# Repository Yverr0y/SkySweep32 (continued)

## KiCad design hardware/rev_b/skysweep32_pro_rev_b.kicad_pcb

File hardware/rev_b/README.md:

# SkySweep32 Pro Rev B Hardware Architecture

> **EXPERIMENTAL / UNVERIFIED / DO NOT ORDER**
>
> This directory contains a failed Rev B design baseline under engineering
> audit. The checked-in ERC report has 8 warnings and the checked-in DRC report
> has 375 violations, including mounting-hole/component conflicts. Generated
> STEP/STL files and previews do not prove mechanical fit. Do not manufacture
> this revision. See [`HARDWARE_VALIDATION_REPORT.md`](HARDWARE_VALIDATION_REPORT.md).

---

## Key Hardware Improvements (Rev A → Rev B)

1. **Integrated ESP32-S3 MCU**: Replaced generic DevKit module with an integrated **ESP32-S3-WROOM-1-N8** (8 MB flash, no PSRAM) to prevent strap-pin conflicts on GPIO35–37.
2. **Sub-GHz Transceiver Upgrade**: Replaced obsolete 433 MHz CC1101 module with Ebyte **E07-900M10S** (855–925 MHz SMD castellated module) with IPEX pigtail to panel SMA.
3. **Four-Layer PCB Architecture**: Stackup:
   - `L1 (F.Cu)`: High-speed signal routing and local power traces
   - `L2 (In1.Cu)`: Uninterrupted solid Ground plane (`GND`)
   - `L3 (In2.Cu)`: Split Power plane (`3V3_MAIN` / `VBUS_PROTECTED`)
   - `B.Cu`: Secondary signal routing
4. **Enhanced Power Management**:
   - TI **LM73100** eFuse protection (5.5 A, OVLO, UVLO, IMON)
   - Diodes Inc **AP63203WU-7** 2.0 A synchronous buck converter (3.3 V output, 44% headroom)
   - Dedicated low-pass RC filters on all RF power branches
5. **No Decorative SMA Connectors**: Every SMA bulkhead maps 1:1 to an active radio module.
6. **Sentinel Enclosure Rev B**: Generated enclosure concept; assembly fit and interference are unverified.

---

## File Inventory

| File / Path | Description |
|---|---|
| [`skysweep32_pro_rev_b.kicad_sch`](skysweep32_pro_rev_b.kicad_sch) | Native KiCad 10 schematic |
| [`skysweep32_pro_rev_b.kicad_pcb`](skysweep32_pro_rev_b.kicad_pcb) | Native 4-layer KiCad 10 PCB baseline; checked-in DRC currently fails |
| [`generate_pcb.py`](generate_pcb.py) | Automated PCB generation and net-contract assertion script |
| [`build_case_rev_b.py`](build_case_rev_b.py) | FreeCAD Python 3D enclosure CAD synthesis script |
| [`skysweep32_pro_rev_b.step`](skysweep32_pro_rev_b.step) | 3D PCB Assembly STEP file (5.1 MB) |
| [`enclosures/skysweep32_pro_case_bottom_rev_b.stl`](enclosures/skysweep32_pro_case_bottom_rev_b.stl) | Sentinel Enclosure Bottom Case (3D Printable STL) |
| [`enclosures/skysweep32_pro_case_lid_rev_b.stl`](enclosures/skysweep32_pro_case_lid_rev_b.stl) | Sentinel Enclosure Top Lid Case (3D Printable STL) |
| [`HARDWARE_VALIDATION_REPORT.md`](HARDWARE_VALIDATION_REPORT.md) | Evidence-backed current failure and maturity status |

---

## Previews

### 3D PCB Assembly Preview

### Sentinel Enclosure
- Bottom case volume: **43 866.27 mm³**
- Lid case volume: **34 725.00 mm³**
- Wall thickness: **2.5 mm**
- Outer dimensions: **128 × 88 × 28.5 mm**

---

## Build & Synthesis Commands

Generate PCB baseline:
```bash
python hardware/rev_b/generate_pcb.py
```

Run KiCad DRC check:
```bash
kicad-cli pcb drc hardware/rev_b/skysweep32_pro_rev_b.kicad_pcb
```

Generate 3D Enclosure STEP/STL files:
```bash
python hardware/rev_b/build_case_rev_b.py
```

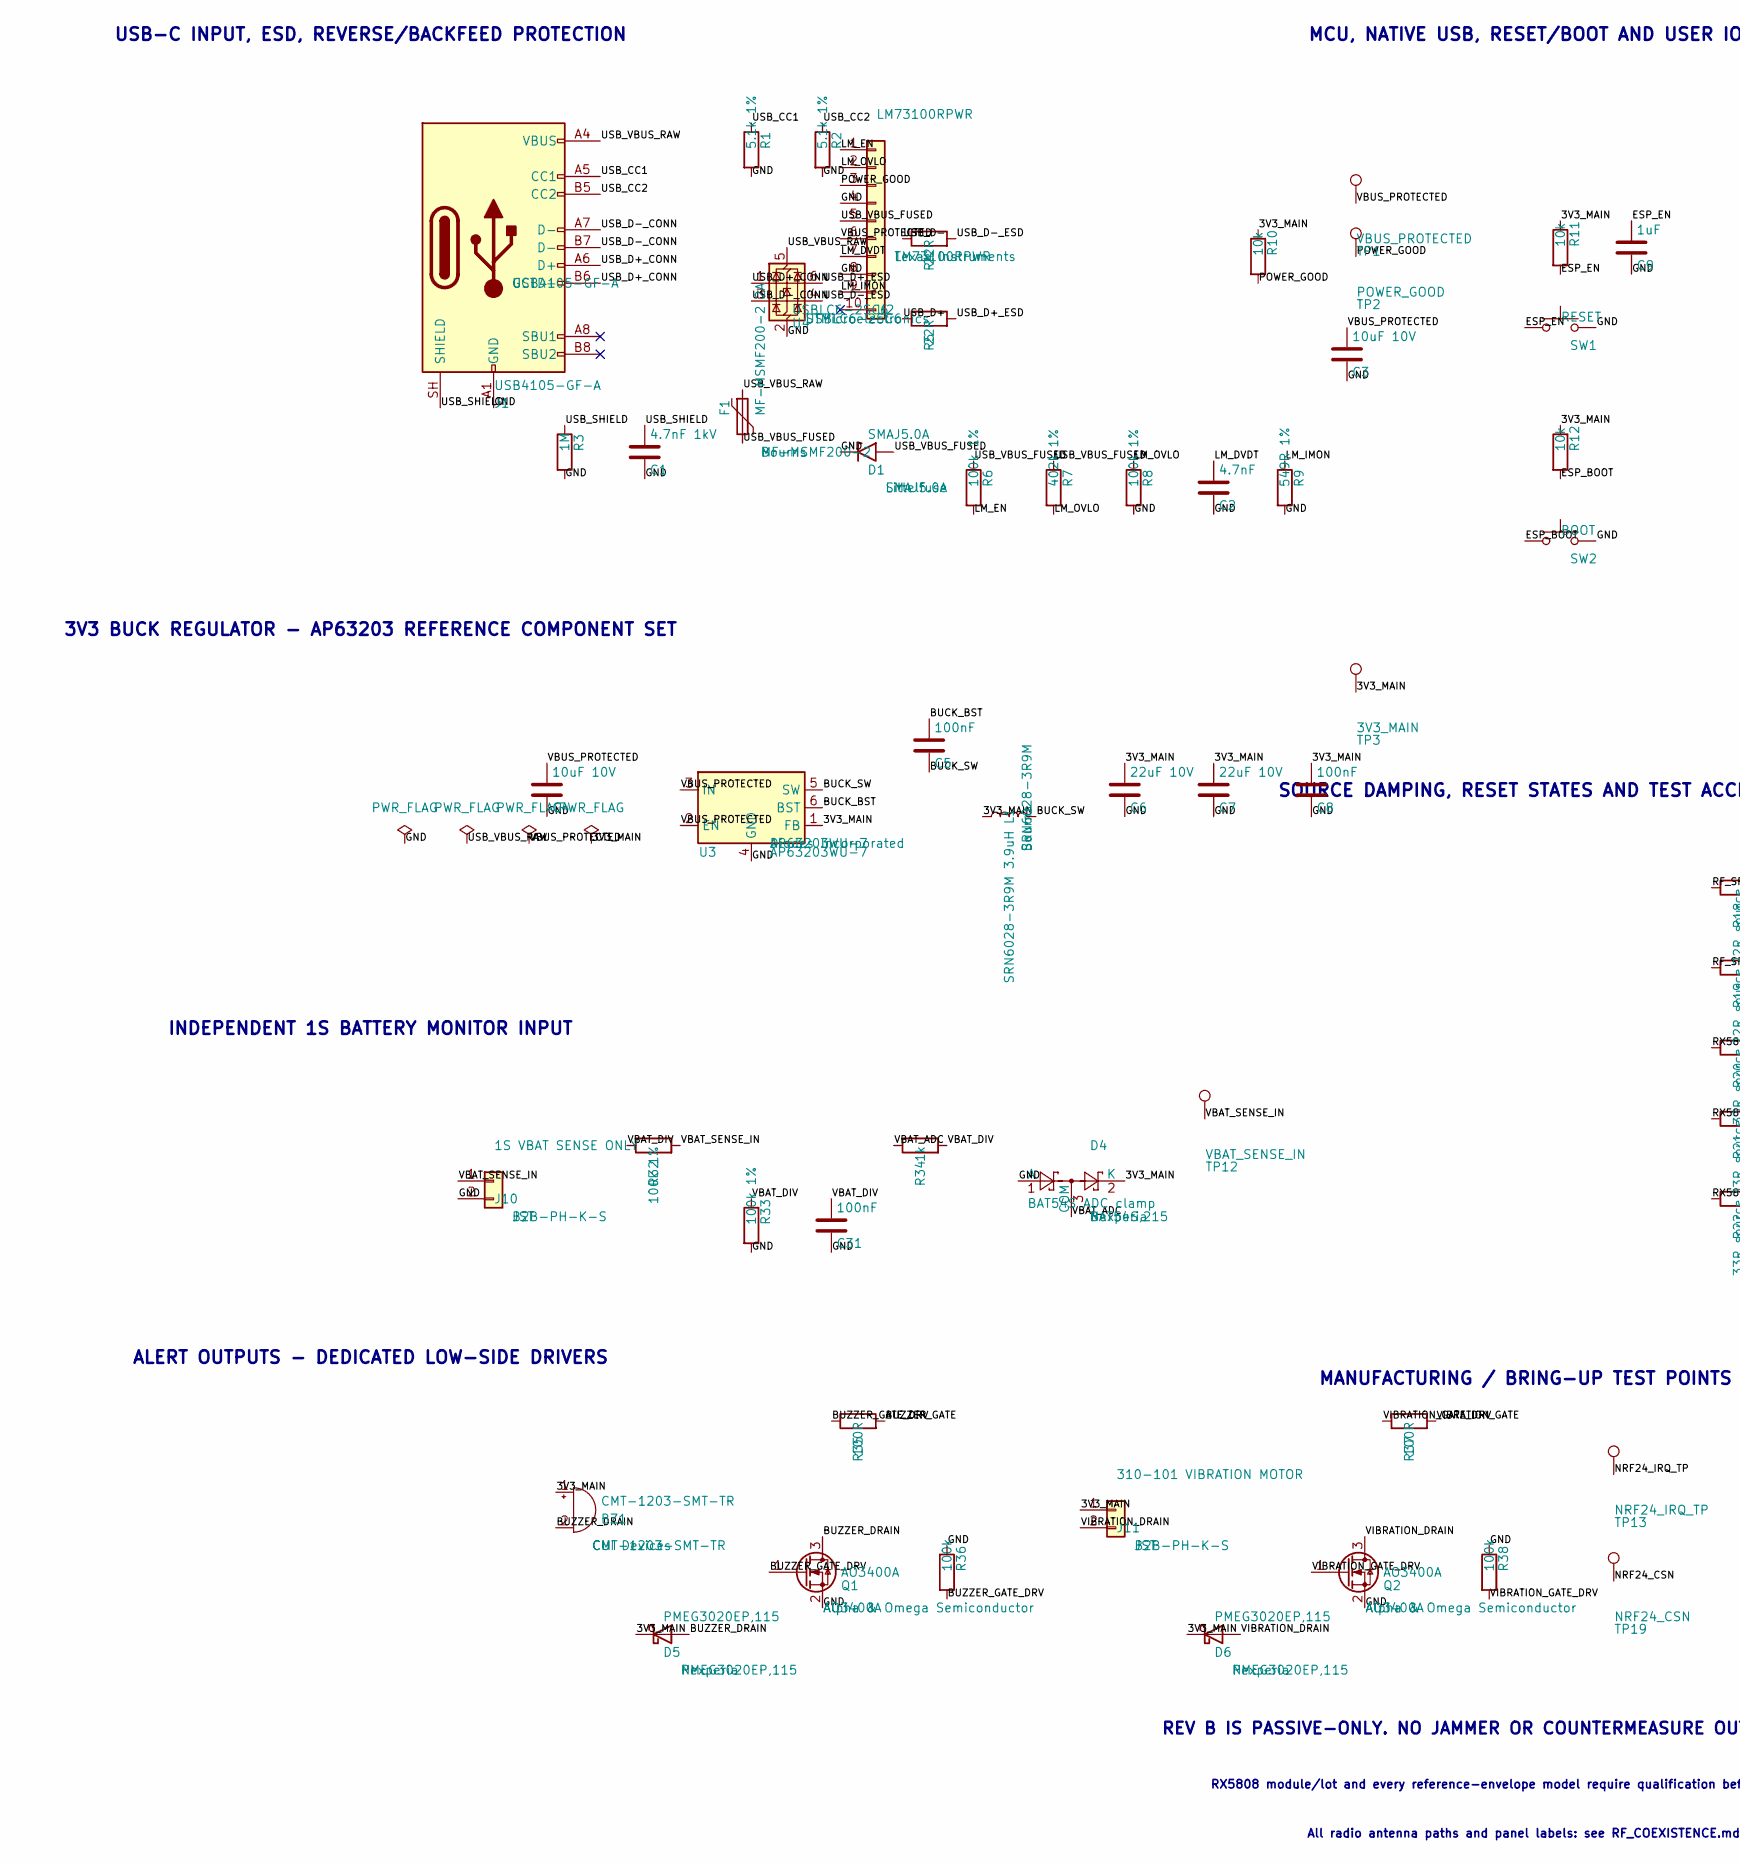
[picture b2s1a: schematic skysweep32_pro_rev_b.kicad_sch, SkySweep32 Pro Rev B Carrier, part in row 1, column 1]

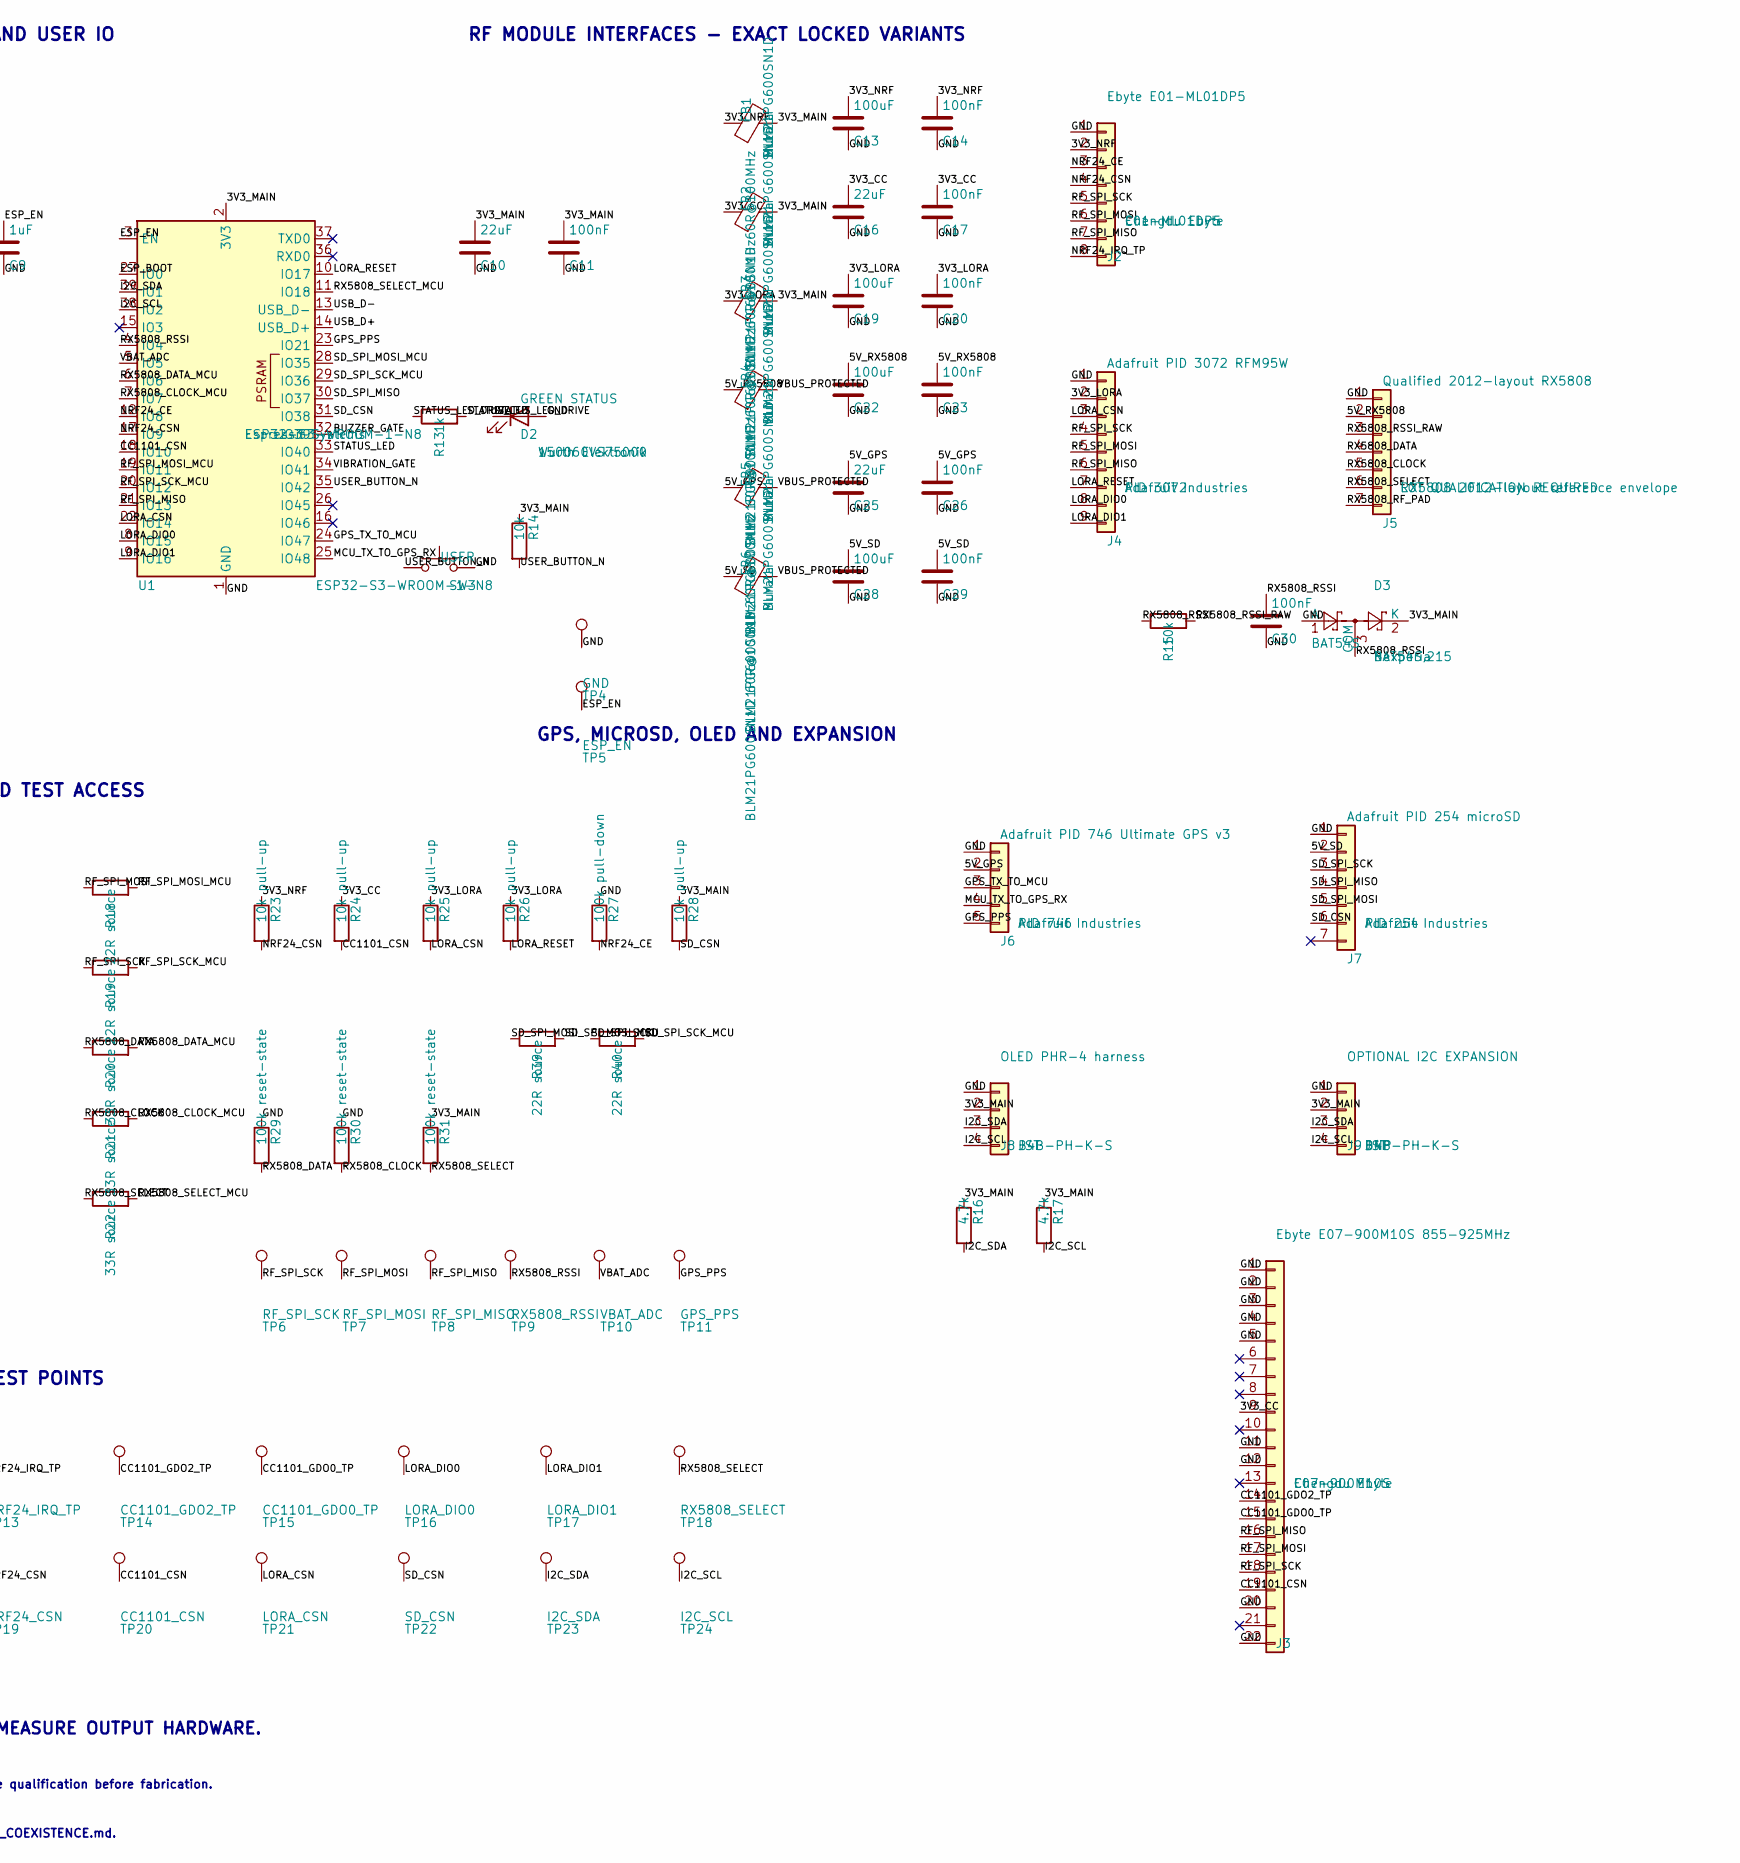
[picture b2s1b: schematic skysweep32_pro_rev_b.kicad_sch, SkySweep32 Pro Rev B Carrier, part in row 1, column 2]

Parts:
BZ1: CMT-1203-SMT-TR; Buzzer_CUI_CMT-1203-SMT-TR; MPN CMT-1203-SMT-TR
C1: 4.7nF 1kV; C_0603_1608Metric
C2: 4.7nF; C_0603_1608Metric
C3, C4: 10uF 10V; C_0805_2012Metric
C5, C8, C11, C14, C17, C20, C23, C26, C29, C30, C31: 100nF; C_0603_1608Metric
C6, C7: 22uF 10V; C_1210_3225Metric
C9: 1uF; C_0603_1608Metric
C10, C16, C25: 22uF; C_1210_3225Metric
C13, C19, C22, C28: 100uF; C_1210_3225Metric
D1: SMAJ5.0A; D_SMA; MPN SMAJ5.0A
D2: GREEN STATUS; LED_0603_1608Metric; MPN 150060VS75000
D3: BAT54S; SOT-23; MPN BAT54S,215
D4: BAT54S ADC clamp; SOT-23; MPN BAT54S,215
D5, D6: PMEG3020EP,115; D_SOD-128; MPN PMEG3020EP,115
F1: MF-MSMF200-2 2A; Fuse_1812_4532Metric; MPN MF-MSMF200-2
FB1, FB2, FB3, FB4, FB5, FB6: BLM21PG600SN1D 60R@100MHz; R_0805_2012Metric; MPN BLM21PG600SN1D
J1: USB4105-GF-A; USB_C_Receptacle_GCT_USB4105-xx-A_16P_TopMnt_Horizontal; MPN USB4105-GF-A
J2: Ebyte E01-ML01DP5; Module_Ebyte_E01_ML01DP5; MPN E01-ML01DP5
J3: Ebyte E07-900M10S 855-925MHz; Module_Ebyte_E07_900M10S; MPN E07-900M10S
J4: Adafruit PID 3072 RFM95W; Module_Adafruit_RFM95W_PID3072; MPN PID 3072
J5: Qualified 2012-layout RX5808; Module_RX5808_2012_QUALIFIED; MPN RX5808 2012-layout reference envelope
J6: Adafruit PID 746 Ultimate GPS v3; Module_Adafruit_GPS_PID746; MPN PID 746
J7: Adafruit PID 254 microSD; Module_Adafruit_MicroSD_PID254; MPN PID 254
J8: OLED PHR-4 harness; JST_PH_B4B-PH-K_1x04_P2.00mm_Vertical; MPN B4B-PH-K-S
J9: OPTIONAL I2C EXPANSION; JST_PH_B4B-PH-K_1x04_P2.00mm_Vertical; MPN B4B-PH-K-S
J10: 1S VBAT SENSE ONLY; JST_PH_B2B-PH-K_1x02_P2.00mm_Vertical; MPN B2B-PH-K-S
J11: 310-101 VIBRATION MOTOR; JST_PH_B2B-PH-K_1x02_P2.00mm_Vertical; MPN B2B-PH-K-S
L1: SRN6028-3R9M 3.9uH; L_Bourns-SRN6028; MPN SRN6028-3R9M
Q1, Q2: AO3400A; SOT-23; MPN AO3400A
R1, R2: 5.1k 1%; R_0603_1608Metric
R3: 1M; R_0603_1608Metric
R4, R5: 22R; R_0603_1608Metric
R6, R8, R32, R33: 100k 1%; R_0603_1608Metric
R7: 402k 1%; R_0603_1608Metric
R9: 549R 1%; R_0603_1608Metric
R10, R11, R12, R14, R15: 10k; R_0603_1608Metric
R13, R34: 1k; R_0603_1608Metric
R16, R17: 4.7k; R_0603_1608Metric
R18, R19, R39, R40: 22R source; R_0603_1608Metric
R20, R21, R22: 33R source; R_0603_1608Metric
R23, R24, R25, R26, R28: 10k pull-up; R_0603_1608Metric
R27: 100k pull-down; R_0603_1608Metric
R29, R30, R31: 100k reset-state; R_0603_1608Metric
R35, R37: 100R; R_0603_1608Metric
R36, R38: 100k; R_0603_1608Metric
SW1: RESET; SW_SPST_PTS810
SW2: BOOT; SW_SPST_PTS810
SW3: USER; SW_SPST_PTS810
TP1: VBUS_PROTECTED; TestPoint_Plated_Hole_D2.0mm
TP2: POWER_GOOD; TestPoint_Plated_Hole_D2.0mm
TP3: 3V3_MAIN; TestPoint_Plated_Hole_D2.0mm
TP4: GND; TestPoint_Plated_Hole_D2.0mm
TP5: ESP_EN; TestPoint_Plated_Hole_D2.0mm
TP6: RF_SPI_SCK; TestPoint_Plated_Hole_D2.0mm
TP7: RF_SPI_MOSI; TestPoint_Plated_Hole_D2.0mm
TP8: RF_SPI_MISO; TestPoint_Plated_Hole_D2.0mm
TP9: RX5808_RSSI; TestPoint_Plated_Hole_D2.0mm
TP10: VBAT_ADC; TestPoint_Plated_Hole_D2.0mm
TP11: GPS_PPS; TestPoint_Plated_Hole_D2.0mm
TP12: VBAT_SENSE_IN; TestPoint_Plated_Hole_D2.0mm
TP13: NRF24_IRQ_TP; TestPoint_Plated_Hole_D2.0mm
TP14: CC1101_GDO2_TP; TestPoint_Plated_Hole_D2.0mm
TP15: CC1101_GDO0_TP; TestPoint_Plated_Hole_D2.0mm
TP16: LORA_DIO0; TestPoint_Plated_Hole_D2.0mm
TP17: LORA_DIO1; TestPoint_Plated_Hole_D2.0mm
TP18: RX5808_SELECT; TestPoint_Plated_Hole_D2.0mm
TP19: NRF24_CSN; TestPoint_Plated_Hole_D2.0mm
TP20: CC1101_CSN; TestPoint_Plated_Hole_D2.0mm
TP21: LORA_CSN; TestPoint_Plated_Hole_D2.0mm
TP22: SD_CSN; TestPoint_Plated_Hole_D2.0mm
TP23: I2C_SDA; TestPoint_Plated_Hole_D2.0mm
TP24: I2C_SCL; TestPoint_Plated_Hole_D2.0mm
U1: ESP32-S3-WROOM-1-N8; ESP32-S3-WROOM-1; MPN ESP32-S3-WROOM-1-N8
U2: LM73100RPWR; Texas_RUN0010A_WQFN-10_2x2mm_P0.5mm; MPN LM73100RPWR
U3: AP63203WU-7; TSOT-23-6; MPN AP63203WU-7
U4: USBLC6-2SC6; SOT-23-6; MPN USBLC6-2SC6

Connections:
3V3_CC: C16.1, C17.1, FB2.1, J3.9, R24.1
3V3_LORA: C19.1, C20.1, FB3.1, J4.2, R25.1, R26.1
3V3_MAIN: BZ1.1 (+), C6.1, C7.1, C8.1, C10.1, C11.1, D3.2 (K), D4.2 (K), D5.1 (K), D6.1 (K), FB1.2, FB2.2, FB3.2, J8.2, J9.2, J11.1, L1.1, R10.1, R11.1, R12.1, R14.1, R16.1, R17.1, R28.1, R31.1, TP3.1, U1.2 (3V3), U3.1 (FB)
3V3_NRF: C13.1, C14.1, FB1.1, J2.2, R23.1
5V_GPS: C25.1, C26.1, FB5.1, J6.2
5V_RX5808: C22.1, C23.1, FB4.1, J5.2
5V_SD: C28.1, C29.1, FB6.1, J7.2
BUCK_BST: C5.1, U3.6 (BST)
BUCK_SW: C5.2, L1.2, U3.5 (SW)
BUZZER_DRAIN: BZ1.2 (-), D5.2 (A), Q1.3 (D)
BUZZER_GATE: R35.2, U1.32 (IO39)
BUZZER_GATE_DRV: Q1.1 (G), R35.1, R36.2
CC1101_CSN: J3.19, R24.2, TP20.1, U1.18 (IO10)
CC1101_GDO0_TP: J3.15, TP15.1
CC1101_GDO2_TP: J3.14, TP14.1
ESP_BOOT: R12.2, SW2.1, U1.27 (IO0)
ESP_EN: C9.1, R11.2, SW1.1, TP5.1, U1.3 (EN)
GND: C1.2, C2.2, C3.2, C4.2, C6.2, C7.2, C8.2, C9.2, C10.2, C11.2, C13.2, C14.2, C16.2, C17.2, C19.2, C20.2, C22.2, C23.2, C25.2, C26.2, C28.2, C29.2, C30.2, C31.2, D1.1 (A1), D2.2 (A), D3.1 (A), D4.1 (A), J1.A1 (GND), J1.A12 (GND), J1.B1 (GND), J1.B12 (GND), J2.1, J3.1, J3.2, J3.3, J3.4, J3.5, J3.11, J3.12, J3.20, J3.22, J4.1, J5.1, J6.1, J7.1, J8.1, J9.1, J10.2, Q1.2 (S), Q2.2 (S), R1.2, R2.2, R3.2, R8.2, R9.2, R27.1, R29.1, R30.1, R33.2, R36.1, R38.1, SW1.2, SW2.2, SW3.2, TP4.1, U1.1 (GND), U1.40 (GND), U1.41 (GND), U2.4, U2.8, U3.4 (GND), U4.2 (GND)
GPS_PPS: J6.5, TP11.1, U1.23 (IO21)
GPS_TX_TO_MCU: J6.3, U1.24 (IO47)
I2C_SCL: J8.4, J9.4, R17.2, TP24.1, U1.38 (IO2)
I2C_SDA: J8.3, J9.3, R16.2, TP23.1, U1.39 (IO1)
LM_DVDT: C2.1, U2.7
LM_EN: R6.2, U2.1
LM_IMON: R9.1, U2.9
LM_OVLO: R7.2, R8.1, U2.2
LORA_CSN: J4.3, R25.2, TP21.1, U1.22 (IO14)
LORA_DIO0: J4.8, TP16.1, U1.8 (IO15)
LORA_DIO1: J4.9, TP17.1, U1.9 (IO16)
LORA_RESET: J4.7, R26.2, U1.10 (IO17)
MCU_TX_TO_GPS_RX: J6.4, U1.25 (IO48)
NRF24_CE: J2.3, R27.2, U1.12 (IO8)
NRF24_CSN: J2.4, R23.2, TP19.1, U1.17 (IO9)
NRF24_IRQ_TP: J2.8, TP13.1
POWER_GOOD: R10.2, TP2.1, U2.3
RF_SPI_MISO: J2.7, J3.16, J4.6, TP8.1, U1.21 (IO13)
RF_SPI_MOSI: J2.6, J3.17, J4.5, R18.1, TP7.1
RF_SPI_MOSI_MCU: R18.2, U1.19 (IO11)
RF_SPI_SCK: J2.5, J3.18, J4.4, R19.1, TP6.1
RF_SPI_SCK_MCU: R19.2, U1.20 (IO12)
RX5808_CLOCK: J5.5, R21.1, R30.2
RX5808_CLOCK_MCU: R21.2, U1.7 (IO7)
RX5808_DATA: J5.4, R20.1, R29.2
RX5808_DATA_MCU: R20.2, U1.6 (IO6)
RX5808_RF_PAD: J5.7
RX5808_RSSI: C30.1, D3.3 (COM), R15.1, TP9.1, U1.4 (IO4)
RX5808_RSSI_RAW: J5.3, R15.2
RX5808_SELECT: J5.6, R22.1, R31.2, TP18.1
RX5808_SELECT_MCU: R22.2, U1.11 (IO18)
SD_CSN: J7.6, R28.2, TP22.1, U1.31 (IO38)
SD_SPI_MISO: J7.4, U1.30 (IO37)
SD_SPI_MOSI: J7.5, R39.1
SD_SPI_MOSI_MCU: R39.2, U1.28 (IO35)
SD_SPI_SCK: J7.3, R40.1
SD_SPI_SCK_MCU: R40.2, U1.29 (IO36)
STATUS_LED: R13.2, U1.33 (IO40)
STATUS_LED_DRIVE: D2.1 (K), R13.1
USB_CC1: J1.A5 (CC1), R1.1
USB_CC2: J1.B5 (CC2), R2.1
USB_D+: R5.1, U1.14 (USB_D+)
USB_D+_CONN: J1.A6 (D+), J1.B6 (D+), U4.1 (I/O1)
USB_D+_ESD: R5.2, U4.6 (I/O1)
USB_D-: R4.1, U1.13 (USB_D-)
USB_D-_CONN: J1.A7 (D-), J1.B7 (D-), U4.3 (I/O2)
USB_D-_ESD: R4.2, U4.4 (I/O2)
USB_SHIELD: C1.1, J1.SH (SHIELD), R3.1
USB_VBUS_FUSED: D1.2 (A2), F1.2, R6.1, R7.1, U2.5
USB_VBUS_RAW: F1.1, J1.A4 (VBUS), J1.A9 (VBUS), J1.B4 (VBUS), J1.B9 (VBUS), U4.5 (VBUS)
USER_BUTTON_N: R14.2, SW3.1, U1.35 (IO42)
VBAT_ADC: D4.3 (COM), R34.1, TP10.1, U1.5 (IO5)
VBAT_DIV: C31.1, R32.1, R33.1, R34.2
VBAT_SENSE_IN: J10.1, R32.2, TP12.1
VBUS_PROTECTED: C3.1, C4.1, FB4.2, FB5.2, FB6.2, TP1.1, U2.6, U3.2 (EN), U3.3 (IN)
VIBRATION_DRAIN: D6.2 (A), J11.2, Q2.3 (D)
VIBRATION_GATE: R37.2, U1.34 (IO41)
VIBRATION_GATE_DRV: Q2.1 (G), R37.1, R38.2

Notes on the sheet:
USB-C INPUT, ESD, REVERSE/BACKFEED PROTECTION
3V3 BUCK REGULATOR - AP63203 REFERENCE COMPONENT SET
MCU, NATIVE USB, RESET/BOOT AND USER IO
RF MODULE INTERFACES - EXACT LOCKED VARIANTS
GPS, MICROSD, OLED AND EXPANSION
SOURCE DAMPING, RESET STATES AND TEST ACCESS
INDEPENDENT 1S BATTERY MONITOR INPUT
ALERT OUTPUTS - DEDICATED LOW-SIDE DRIVERS
MANUFACTURING / BRING-UP TEST POINTS
REV B IS PASSIVE-ONLY. NO JAMMER OR COUNTERMEASURE OUTPUT HARDWARE.
RX5808 module/lot and every reference-envelope model require qualification before fabrication.
All radio antenna paths and panel labels: see RF_COEXISTENCE.md.

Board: 4 copper layers, 128 parts (0 on the bottom side), 75 nets, no tracks yet.

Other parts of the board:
H1, H2, H3, H4: M3 NPTH; MountingHole_3.2mm_M3

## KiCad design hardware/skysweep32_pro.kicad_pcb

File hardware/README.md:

# SkySweep32 Hardware Revisions

## Canonical current design: Rev C

**Rev C status: READY FOR FIRST PHYSICAL PROTOTYPE — NOT PRODUCTION
VALIDATED.**

[`rev_c/`](rev_c/) is the only current hardware source. Its native KiCad 10
schematic and four-layer PCB, exact BOM, generated fabrication package, complete
PCBA STEP, co-designed enclosure, firmware pin contract, and validation evidence
are documented in [`rev_c/README.md`](rev_c/README.md).

Run the complete local gate from the repository root:

```bash
python hardware/verify.py
```

Passing this command establishes encoded ERC/DRC, CAD interference, export, and
firmware-build results. It does not establish an assembled, bench-tested,
field-tested, compliant, or production-validated device.

## Revision authority

| Revision | Status | Use |
|---|---|---|
| [`rev_c/`](rev_c/) | Ready for first physical prototype | Current engineering source and prototype fabrication package |
| [`rev_b/`](rev_b/) | Failed/unverified; do not order | Historical audit evidence only |
| Root-level files / [`enclosures/`](enclosures/) | Legacy Rev A; do not order | Historical issue #10 parser-compatibility artifacts only |

Rev C is electrically, mechanically, and firmware incompatible with Rev A and
Rev B. No legacy pin map, BOM, enclosure, generated report, or manufacturing
file applies to Rev C.

## Historical material

Everything outside `rev_c/` is retained only for historical review:

- [`rev_b/`](rev_b/) documents the failed/unverified Rev B baseline;
- root-level KiCad 6 files, generators, previews, and [`enclosures/`](enclosures/)
  are legacy Rev A / issue #10 parser-compatibility artifacts.

They are **not** part of any Rev C manufacture, assembly, enclosure, pin-map,
or firmware workflow. Do not regenerate them unless investigating history. The
current build path is [`rev_c/BUILD.md`](rev_c/BUILD.md).

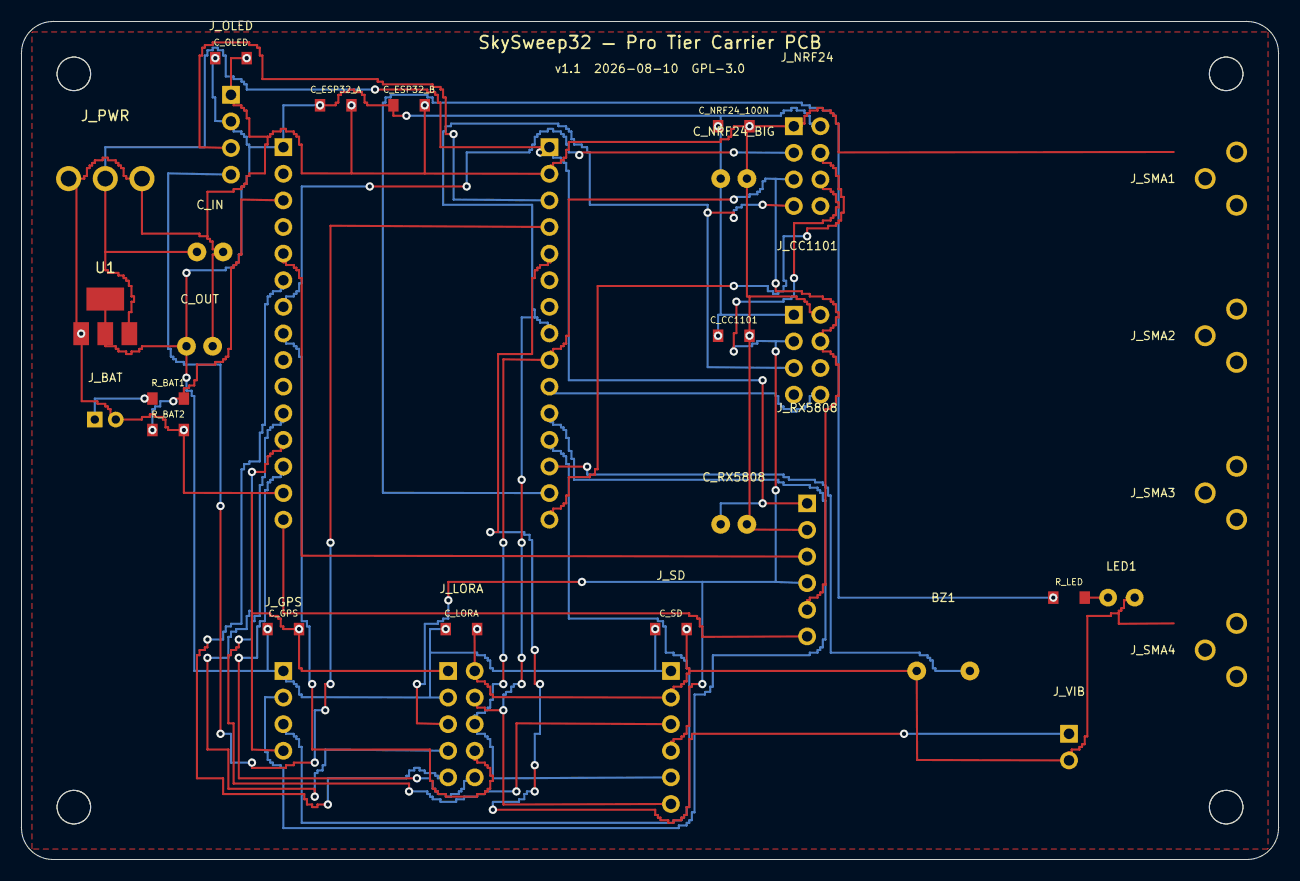
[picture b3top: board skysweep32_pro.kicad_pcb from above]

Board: 2 copper layers, 120.0 x 80.0 mm, 38 parts (0 on the bottom side), 26 nets.

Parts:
BZ1: BUZZER; BZ_12x9.5mm
C_CC1101: 100nF; C_0805_2012Metric
C_ESP32_A, C_ESP32_B: 100nF; C_0805_2012Metric
C_GPS: 100nF; C_0805_2012Metric
C_IN: 100uF/16V; CP_Radial_D6.3mm_P2.50mm
C_LORA: 100nF; C_0805_2012Metric
C_NRF24_100N: 100nF; C_0805_2012Metric
C_NRF24_BIG: 10uF/10V; CP_Radial_D6.3mm_P2.50mm
C_OLED: 100nF; C_0805_2012Metric
C_OUT: 10uF/10V; CP_Radial_D6.3mm_P2.50mm
C_RX5808: 100uF/10V; CP_Radial_D6.3mm_P2.50mm
C_SD: 100nF; C_0805_2012Metric
H1, H2, H3, H4: MH_M3; MountingHole_3.2mm_M3
J_BAT: LIPO IN; JST_PH_B2B-PH-K_1x02_P2.00mm_Vertical
J_CC1101: CC1101 900MHz; PinHeader_2x04_P2.54mm_Vertical
J_ESP32_L: ESP32 Left; PinHeader_1x15_P2.54mm_Vertical
J_ESP32_R: ESP32 Right; PinHeader_1x15_P2.54mm_Vertical
J_GPS: GPS NEO-6M; PinHeader_1x04_P2.54mm_Vertical
J_LORA: LoRa SX1276; PinHeader_2x05_P2.54mm_Vertical
J_NRF24: NRF24L01+; PinHeader_2x04_P2.54mm_Vertical
J_OLED: OLED SSD1306; PinHeader_1x04_P2.54mm_Vertical
J_PWR: 5V DC IN; BarrelJack_CUI_PJ-102A_Horizontal
J_RX5808: RX5808 5.8GHz; PinHeader_1x06_P2.54mm_Vertical
J_SD: MicroSD SPI; PinHeader_1x06_P2.54mm_Vertical
J_SMA1: 900MHz CC1101; SMA_Amphenol_132289_EdgeMount
J_SMA2: 2.4GHz NRF24; SMA_Amphenol_132289_EdgeMount
J_SMA3: 5.8GHz RX5808; SMA_Amphenol_132289_EdgeMount
J_SMA4: 915MHz LoRa; SMA_Amphenol_132289_EdgeMount
J_VIB: VIBRATION MOTOR (GPIO0); PinHeader_1x02_P2.54mm_Vertical
LED1: LED_RED; LED_D3.0mm
R_BAT1, R_BAT2: 100k; R_0805_2012Metric
R_LED: 330R; R_0805_2012Metric
U1: AMS1117-3.3; SOT-223-3_TabPin2

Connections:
ALERT_LED: J_ESP32_R.14, R_LED.1
BAT_ADC: J_ESP32_L.3, R_BAT1.2, R_BAT2.1
BAT_VRAW: J_BAT.1, R_BAT1.1
BUZZER: BZ1.1, J_ESP32_R.13
CC_CS: J_CC1101.8, J_ESP32_R.10
GND: BZ1.2, C_CC1101.2, C_ESP32_A.2, C_ESP32_B.2, C_GPS.2, C_IN.2, C_LORA.2, C_NRF24_100N.2, C_NRF24_BIG.2, C_OLED.2, C_OUT.2, C_RX5808.2, C_SD.2, J_BAT.2, J_CC1101.2, J_ESP32_L.14, J_ESP32_R.2, J_GPS.4, J_LORA.1, J_LORA.2, J_NRF24.1, J_OLED.1, J_PWR.2, J_PWR.3, J_RX5808.2, J_SD.2, J_SMA1.2, J_SMA1.3, J_SMA2.2, J_SMA2.3, J_SMA3.2, J_SMA3.3, J_SMA4.2, J_SMA4.3, J_VIB.2, LED1.2, R_BAT2.2, U1.1
GPS_RX: J_ESP32_R.12, J_GPS.3
GPS_TX: J_ESP32_R.11, J_GPS.2
I2C_SCL: J_ESP32_R.3, J_OLED.3
I2C_SDA: J_ESP32_R.4, J_OLED.4
LED_ANODE: LED1.1, R_LED.2
LORA_CS: J_ESP32_L.12, J_LORA.7
LORA_DIO0: J_ESP32_L.8, J_LORA.8
LORA_DIO1: J_ESP32_L.6, J_LORA.9
LORA_RST: J_ESP32_L.13, J_LORA.10
NRF_CE: J_ESP32_L.7, J_NRF24.3
NRF_CS: J_ESP32_R.15, J_NRF24.4
RX_CS: J_ESP32_L.15, J_RX5808.6
RX_RSSI: J_ESP32_L.5, J_RX5808.3
SD_CS: J_ESP32_L.11, J_SD.3
SPI_MISO: J_CC1101.5, J_ESP32_R.8, J_LORA.4, J_NRF24.7, J_SD.6
SPI_MOSI: J_CC1101.3, J_LORA.5, J_NRF24.6, J_RX5808.4, J_SD.4
SPI_SCK: J_CC1101.4, J_ESP32_R.9, J_LORA.6, J_NRF24.5, J_RX5808.5, J_SD.5
VCC_3V3: C_CC1101.1, C_ESP32_A.1, C_ESP32_B.1, C_GPS.1, C_LORA.1, C_NRF24_100N.1, C_NRF24_BIG.1, C_OLED.1, C_OUT.1, C_SD.1, J_CC1101.1, J_ESP32_L.1, J_GPS.1, J_LORA.3, J_NRF24.2, J_OLED.2, J_SD.1, U1.2, U1.4
VCC_5V: C_IN.1, C_RX5808.1, J_ESP32_R.1, J_PWR.1, J_RX5808.1, U1.3
VIBRATION: J_ESP32_R.5, J_VIB.1

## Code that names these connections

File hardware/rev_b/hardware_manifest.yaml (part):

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    }
  },
  "signals": {
    "I2C_SDA": {"gpio": 1, "direction": "bidirectional", "firmware_macro": "PIN_I2C_SDA", "net": "/I2C_SDA"},
    "I2C_SCL": {"gpio": 2, "direction": "output", "firmware_macro": "PIN_I2C_SCL", "net": "/I2C_SCL"},
    "RX5808_RSSI": {"gpio": 4, "direction": "analog_input", "firmware_macro": "PIN_RX5808_RSSI", "net": "/RX5808_RSSI_ADC", "adc_unit": 1, "adc_channel": 3},
    "VBAT_ADC": {"gpio": 5, "direction": "analog_input", "firmware_macro": "PIN_VBAT_ADC", "net": "/VBAT_ADC", "adc_unit": 1, "adc_channel": 4},
    "RX5808_DATA": {"gpio": 6, "direction": "output", "firmware_macro": "PIN_RX5808_DATA", "net": "/RX5808_DATA"},
    "RX5808_CLOCK": {"gpio": 7, "direction": "output", "firmware_macro": "PIN_RX5808_CLOCK", "net": "/RX5808_CLOCK"},
    "NRF24_CE": {"gpio": 8, "direction": "output", "firmware_macro": "PIN_NRF24_CE", "net": "/NRF24_CE", "reset_bias": "100k pulldown"},
    "NRF24_CSN": {"gpio": 9, "direction": "output", "firmware_macro": "PIN_NRF24_CS", "net": "/NRF24_CSN", "reset_bias": "10k pullup"},
    "CC1101_CSN": {"gpio": 10, "direction": "output", "firmware_macro": "PIN_CC1101_CS", "net": "/CC1101_CSN", "reset_bias": "10k pullup"},
    "RF_SPI_MOSI": {"gpio": 11, "direction": "output", "firmware_macro": "PIN_SPI_MOSI", "net": "/RF_SPI_MOSI"},
    "RF_SPI_SCK": {"gpio": 12, "direction": "output", "firmware_macro": "PIN_SPI_SCK", "net": "/RF_SPI_SCK"},
    "RF_SPI_MISO": {"gpio": 13, "direction": "input", "firmware_macro": "PIN_SPI_MISO", "net": "/RF_SPI_MISO"},
    "LORA_CSN": {"gpio": 14, "direction": "output", "firmware_macro": "PIN_LORA_CS", "net": "/LORA_CSN", "reset_bias": "10k pullup"},
    "LORA_DIO0": {"gpio": 15, "direction": "input", "firmware_macro": "PIN_LORA_DIO0", "net": "/LORA_DIO0"},
    "LORA_DIO1": {"gpio": 16, "direction": "input", "firmware_macro": "PIN_LORA_DIO1", "net": "/LORA_DIO1"},
    "LORA_RESET": {"gpio": 17, "direction": "output", "firmware_macro": "PIN_LORA_RESET", "net": "/LORA_RESET_N", "reset_bias": "10k pullup"},
    "RX5808_SELECT": {"gpio": 18, "direction": "output", "firmware_macro": "PIN_RX5808_SELECT", "net": "/RX5808_SELECT", "reset_bias": "10k pullup"},
    "GPS_PPS": {"gpio": 21, "direction": "input", "firmware_macro": "PIN_GPS_PPS", "net": "/GPS_PPS"},
    "SD_SPI_MOSI": {"gpio": 35, "direction": "output", "firmware_macro": "PIN_SD_MOSI", "net": "/SD_SPI_MOSI"},
    "SD_SPI_SCK": {"gpio": 36, "direction": "output", "firmware_macro": "PIN_SD_SCK", "net": "/SD_SPI_SCK"},
    "SD_SPI_MISO": {"gpio": 37, "direction": "input", "firmware_macro": "PIN_SD_MISO", "net": "/SD_SPI_MISO"},
    "SD_CSN": {"gpio": 38, "direction": "output", "firmware_macro": "PIN_SD_CS", "net": "/SD_CSN", "reset_bias": "10k pullup"},
    "ALERT_BUZZER": {"gpio": 39, "direction": "output", "firmware_macro": "PIN_BUZZER", "net": "/BUZZER_GATE", "reset_bias": "100k pulldown"},
    "ALERT_LED": {"gpio": 40, "direction": "output", "firmware_macro": "PIN_ALERT_LED", "net": "/STATUS_LED"},
    "VIBRATION": {"gpio": 41, "direction": "output", "firmware_macro": "PIN_VIBRATION", "net": "/VIBRATION_GATE", "reset_bias": "100k pulldown"},
    "USER_BUTTON": {"gpio": 42, "direction": "input", "firmware_macro": "PIN_USER_BUTTON", "net": "/USER_BUTTON_N", "reset_bias": "10k pullup"},
    "GPS_RX": {"gpio": 47, "direction": "input", "firmware_macro": "PIN_GPS_RX", "net": "/GPS_TX_TO_MCU"},
    "GPS_TX": {"gpio": 48, "direction": "output", "firmware_macro": "PIN_GPS_TX", "net": "/MCU_TX_TO_GPS_RX"}
  },
  "modules": {
    "MCU1": {
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      "rail": "3V3_MAIN",
      "design_current_ma": 130,
      "connector": "1x8 through-hole row, 2.54mm",
      "module_pins": {"1": "GND", "2": "3V3_MAIN", "3": "NRF24_CE", "4": "NRF24_CSN", "5": "RF_SPI_SCK", "6": "RF_SPI_MOSI", "7": "RF_SPI_MISO", "8": "TP_NRF24_IRQ"},
      "antenna": "module_native_sma",
      "mechanical_mm": [18.0, 33.4]
    },
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      "rail": "VBUS_PROTECTED",
      "design_current_ma": 200,
      "connector": "8 pads qualified from physical sample",
      "module_pins": {"GND": "GND", "5V": "VBUS_PROTECTED", "DATA": "RX5808_DATA", "CLOCK": "RX5808_CLOCK", "SELECT": "RX5808_SELECT", "RSSI": "RX5808_RSSI", "RF": "RX5808_RF_COAX", "VIDEO": "NC"},
      "antenna": "solder_pad_to_rg316_panel_sma",
      "qualification": "A physical seller/lot sample must match the 2012 OpenSource Hobbies pinout and envelope before footprint release",
      "mechanical_mm": [28.0, 23.0, 5.0]
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      "part_number": "PID 3072 RFM95W 915 MHz breakout",
      "rail": "3V3_MAIN",
      "design_current_ma": 130,
      "module_pins": {"VIN": "3V3_MAIN", "GND": "GND", "SCK": "RF_SPI_SCK", "MOSI": "RF_SPI_MOSI", "MISO": "RF_SPI_MISO", "CS": "LORA_CSN", "G0": "LORA_DIO0", "G1": "LORA_DIO1", "RST": "LORA_RESET"},
      "antenna": "ufl_to_rg178_panel_sma",
      "mechanical_mm": [29.0, 25.0]
    },
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      "part_number": "PID 746 Ultimate GPS v3 MTK3339",
      "rail": "VBUS_PROTECTED",
      "design_current_ma": 50,
      "module_pins": {"VIN": "VBUS_PROTECTED", "GND": "GND", "TX": "GPS_RX", "RX": "GPS_TX", "PPS": "GPS_PPS"},
      "antenna": "integrated_patch",
      "mechanical_mm": [25.5, 35.0, 6.5]
    },
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      "part_number": "PID 254 microSD breakout",
      "rail": "VBUS_PROTECTED",
      "design_current_ma": 200,
      "module_pins": {"5V": "VBUS_PROTECTED", "GND": "GND", "CLK": "SD_SPI_SCK", "DO": "SD_SPI_MISO", "DI": "SD_SPI_MOSI", "CS": "SD_CSN"},
      "mechanical_mm": [31.85, 25.4, 3.75],
      "service_access": "push-push card edge exposed through enclosure"
    },
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      "rail": "3V3_MAIN",
      "design_current_ma": 50,
      "connector": "B4B-PH-K-S to PHR-4 keyed harness",
      "module_pins": {"GND": "GND", "VIN": "3V3_MAIN", "SDA": "I2C_SDA", "SCL": "I2C_SCL"},
      "mechanical_mm": [29.2, 26.7, 6.2]
    },
    "EXP1": {
      "function": "optional_i2c_expansion",
      "part_number": "JST B4B-PH-K-S",
      "rail": "3V3_MAIN",
      "module_pins": {"1": "GND", "2": "3V3_MAIN", "3": "I2C_SDA", "4": "I2C_SCL"},
      "fitted": false
    }
  },
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
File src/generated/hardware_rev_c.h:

// Generated by scripts/generate_rev_c_pinmap.py; do not edit.
// Source: hardware/rev_c/hardware_manifest.json
#pragma once

#define BOARD_SKYSWEEP32_REV_C 1
#define PROFILE_PASSIVE_MONITOR 1

#define PIN_I2C_SDA            1  // I2C_SDA
#define PIN_I2C_SCL            2  // I2C_SCL
#define PIN_SD_DETECT          4  // SD_DETECT
#define PIN_RX5808_RSSI        5  // RX5808_RSSI
#define PIN_RX5808_CH1         6  // RX5808_CH1
#define PIN_RX5808_CH2         7  // RX5808_CH2
#define PIN_SX1281_BUSY        8  // SX1281_BUSY
#define PIN_SX1281_CS          9  // SX1281_CSN
#define PIN_CC1101_CS          10 // CC1101_CSN
#define PIN_SPI_MOSI           11 // RF_SPI_MOSI
#define PIN_SPI_SCK            12 // RF_SPI_SCK
#define PIN_SPI_MISO           13 // RF_SPI_MISO
#define PIN_RX5808_CH3         14 // RX5808_CH3
#define PIN_CC1101_GDO0        15 // CC1101_GDO0
#define PIN_CC1101_GDO2        16 // CC1101_GDO2
#define PIN_SX1281_RESET       17 // SX1281_RESET
#define PIN_SX1281_DIO1        18 // SX1281_DIO1
#define PIN_GPS_PPS            21 // GPS_PPS
#define PIN_SD_CS              38 // SD_CSN
#define PIN_BUZZER             39 // ALERT_BUZZER
#define PIN_ALERT_LED          40 // ALERT_LED
#define PIN_VIBRATION          41 // VIBRATION
#define PIN_USER_BUTTON        42 // USER_BUTTON
#define PIN_GPS_RX             47 // GPS_RX
#define PIN_GPS_TX             48 // GPS_TX
#define PIN_SD_MOSI           PIN_SPI_MOSI // shared SPI data
#define PIN_SD_MISO           PIN_SPI_MISO // shared SPI data
#define PIN_SD_SCK            PIN_SPI_SCK  // shared SPI clock

#define GPS_BAUD_RATE          9600
#define GPS_UPDATE_INTERVAL    1000

#if defined(TIER_JUGGERNAUT) || defined(ENABLE_COUNTERMEASURES)
#error "Rev C is passive-only and has no countermeasure hardware"
#endif
#if defined(MODULE_NRF24) || defined(MODULE_LORA) || defined(MODULE_ML)
#error "Rev C does not implement nRF24L01+, LoRa, or TinyML hardware/features"
#endif
#ifdef MODULE_ACOUSTIC
#error "Rev C does not route an I2S acoustic input"
#endif

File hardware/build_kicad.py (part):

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    1:  "GND",
    2:  "VCC_5V",
    3:  "VCC_3V3",
    4:  "SPI_MOSI",      # GPIO23
    5:  "SPI_MISO",      # GPIO19
    6:  "SPI_SCK",       # GPIO18
    7:  "NRF_CS",        # GPIO15
    8:  "NRF_CE",        # GPIO32
    9:  "CC_CS",         # GPIO5
    10: "RX_CS",         # GPIO13
    11: "RX_RSSI",       # GPIO34 ADC
    12: "I2C_SDA",       # GPIO21
    13: "I2C_SCL",       # GPIO22
    14: "GPS_RX",        # GPIO16 (ESP RX ← GPS TX)
    15: "GPS_TX",        # GPIO17 (ESP TX → GPS RX)
    16: "LORA_CS",       # GPIO14
    17: "LORA_DIO0",     # GPIO33
    18: "LORA_DIO1",     # GPIO35
    19: "LORA_RST",      # GPIO12
    20: "SD_CS",         # GPIO27
    21: "BUZZER",        # GPIO4
    22: "BAT_ADC",       # GPIO36 (through voltage divider)
    23: "BAT_VRAW",      # Raw battery voltage (before divider)
    24: "ALERT_LED",     # GPIO2
    25: "VIBRATION",     # GPIO0
    26: "LED_ANODE",     # LED current-limited node
}

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    left_nets = {
        1:  3,   # 3V3 → VCC_3V3
        2:  0,   # EN (no net, user controlled)
        3:  22,  # GPIO36 → BAT_ADC
        4:  0,   # GPIO39 (optional I2S data, no Pro header net)
        5:  11,  # GPIO34 → RX_RSSI
        6:  18,  # GPIO35 → LORA_DIO1
        7:  8,   # GPIO32 → NRF_CE
        8:  17,  # GPIO33 → LORA_DIO0
        9:  0,   # GPIO25 (DAC1, unused in Pro)
        10: 0,   # GPIO26 (DAC2, unused in Pro)
        11: 20,  # GPIO27 → SD_CS
        12: 16,  # GPIO14 → LORA_CS
        13: 19,  # GPIO12 → LORA_RST
        14: 1,   # GND
        15: 10,  # GPIO13 → RX_CS
    }
    # Right header net map (pin 1-15, maps to ESP32 pins R1-R15)
    right_nets = {
        1:  2,   # VIN → VCC_5V
        2:  1,   # GND
        3:  13,  # GPIO22 → I2C_SCL
        4:  12,  # GPIO21 → I2C_SDA
        5:  25,  # GPIO0 → VIBRATION (buffered motor driver)
        6:  0,   # GPIO1 (TX0/UART0)
        7:  0,   # GPIO3 (RX0/UART0)
        8:  5,   # GPIO19 → SPI_MISO
        9:  6,   # GPIO18 → SPI_SCK
        10: 9,   # GPIO5  → CC_CS
        11: 15,  # GPIO17 → GPS_TX
        12: 14,  # GPIO16 → GPS_RX
        13: 21,  # GPIO4  → BUZZER
        14: 24,  # GPIO2  → ALERT_LED
        15: 7,   # GPIO15 → NRF_CS
    }

    # Left header at (x, y), Right header at (x + 25.4, y)
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
def vibration_header(x, y):
    return header_1xN(
        "J_VIB", "VIBRATION MOTOR (GPIO0)", x, y, 2,
        {1: 25, 2: 1},
    )

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    # ── Battery connector ─────────────────────────────────────────────────────
    components.append(bat_connector(8, 38))
    # Voltage divider for battery ADC: 100kΩ from VBAT → middle node → 100kΩ → GND
    # Middle node goes to GPIO36 (BAT_ADC)
    # VRAW (23) → R_BAT1 → BAT_ADC (22) → R_BAT2 → GND (1)
    components.append(res_smd(14, 36, "100k", 23, 22, "R_BAT1"))
    components.append(res_smd(14, 39, "100k", 22, 1,  "R_BAT2"))
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
    # ── GPS NEO-6M 1×4 Header ────────────────────────────────────────────────
    # Pin 1=VCC, 2=RX(GPS), 3=TX(GPS), 4=GND
    # GPS TX → ESP GPIO16 (GPS_RX net), GPS RX ← ESP GPIO17 (GPS_TX net)
    gps_nets = {1: 3, 2: 15, 3: 14, 4: 1}
    components.append(header_1xN("J_GPS", "GPS NEO-6M", 25, 62, 4, gps_nets))
    components.append(cap_smd(25, 58, "100nF", 3, 1, "C_GPS"))
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
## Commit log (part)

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2026-06-09 docs: update hardware BOM with search links and fix LoRa/DAC/I2S pinout docs
2026-06-09 feat: compress web dashboard with GZIP and automate tag releases via CI/CD
2026-06-09 feat: add browser-based OTA firmware updates in Web UI
2026-06-09 feat: add stunning GitHub Pages landing page and auto-deploy workflow
2026-06-09 chore: remove custom pages workflow in favor of classic branch deploy
2026-06-09 feat: add anti-theft security watermark using Konami code
2026-06-09 feat: align website license to GPLv3, add SD log downloader card, and compress web dashboard
2026-06-09 chore: add .nojekyll to docs to fix pages build
2026-06-09 chore: add root .nojekyll and clean brackets in docs watermark
2026-06-09 fix: include SD.h in web_server.cpp when MODULE_SD_CARD is defined to fix pro tier build error
2026-06-09 feat: complete LoRa mesh triangulation math, check off TODO, and redesign landing page to premium slate style
2026-06-09 release: bump version to v0.5.1 and add prebuilt binaries
2026-06-09 design: overhaul layout with grid bg, radial ambient lighting, glassmorphic cards, and sky-blue text gradients
2026-06-12 v0.6.0: Tactical release (ATAK, Compass, Stealth, TinyML)
2026-06-12 docs: Update README and Pages with ATAK, Stealth, and ML features
2026-06-12 fix: compilation errors and deprecated ADC macros
2026-06-12 feat: Add TinyML model generator script
